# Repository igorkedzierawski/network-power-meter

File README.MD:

# Power Panel with Built-in Energy Analyzer based on ESP32

## Project Description
This project was realized as part of my engineering thesis at the Warsaw University of Technology. The device measures the voltage and current of connected devices. The measured data is transmitted from the device to a web application, where it is analyzed. In real-time, the application processes the gathered data and presents the electrical parameters and visualizations of the voltage and current waveforms to the user.

The device is controlled via the web application – measurements are read, results are visualized, and analysis is performed there. The operation is intuitive:
1. Connect the device to power.
2. Connect to it via Wi-Fi.
3. Connect the device you want to test.
4. Measurement results and analysis are available in the web interface.

The final result of the project is a ready-to-use IoT device.

## System Architecture
The project consists of three main components:

1. **Meter Controller** (ESP32 + measurement circuit) – responsible for Wi-Fi connectivity, menu handling, and managing the measurement circuit.
2. **Backend (ESP32 HTTP/WebSocket Server)** – allows control of the device via HTTP endpoints and fast transmission of measurement results via WebSocket.
3. **Frontend (Angular)** – the web application responsible for controlling the meter, analyzing the received data, and presenting both calculated values and waveform visualizations.
4. **PCB Design** – connects all physical components of the meter control board.

## Web Interface Functionality
- **View Electrical Parameters and Harmonic Analysis** – real-time display of measurement results for voltage, current, and power, as well as THD coefficient and harmonic analysis.
- **Waveform Visualization** – shows measured waveforms on a virtual oscilloscope.
- **Measurement Channel and System Parameter Configuration** – allows setting different channels and adjusting device parameters.
- **Trigger Selection and Analysis Window Width Adjustment** – stabilizes waveform drawing and adjusts measurement precision.
- **Meter Calibration** – adjusts calibration coefficients and selects network frequency (50/60Hz).

## Repository Structure
- **smm-esp32** – Source code for ESP32 (C, ESP-IDF)
- **smm-frontend** – Web application (Angular, TypeScript)
- **smm-pcb** – PCB design (KiCad)

## Device Photos

### Final Device

### Meter Control Board PCB

### Web Interface in Use

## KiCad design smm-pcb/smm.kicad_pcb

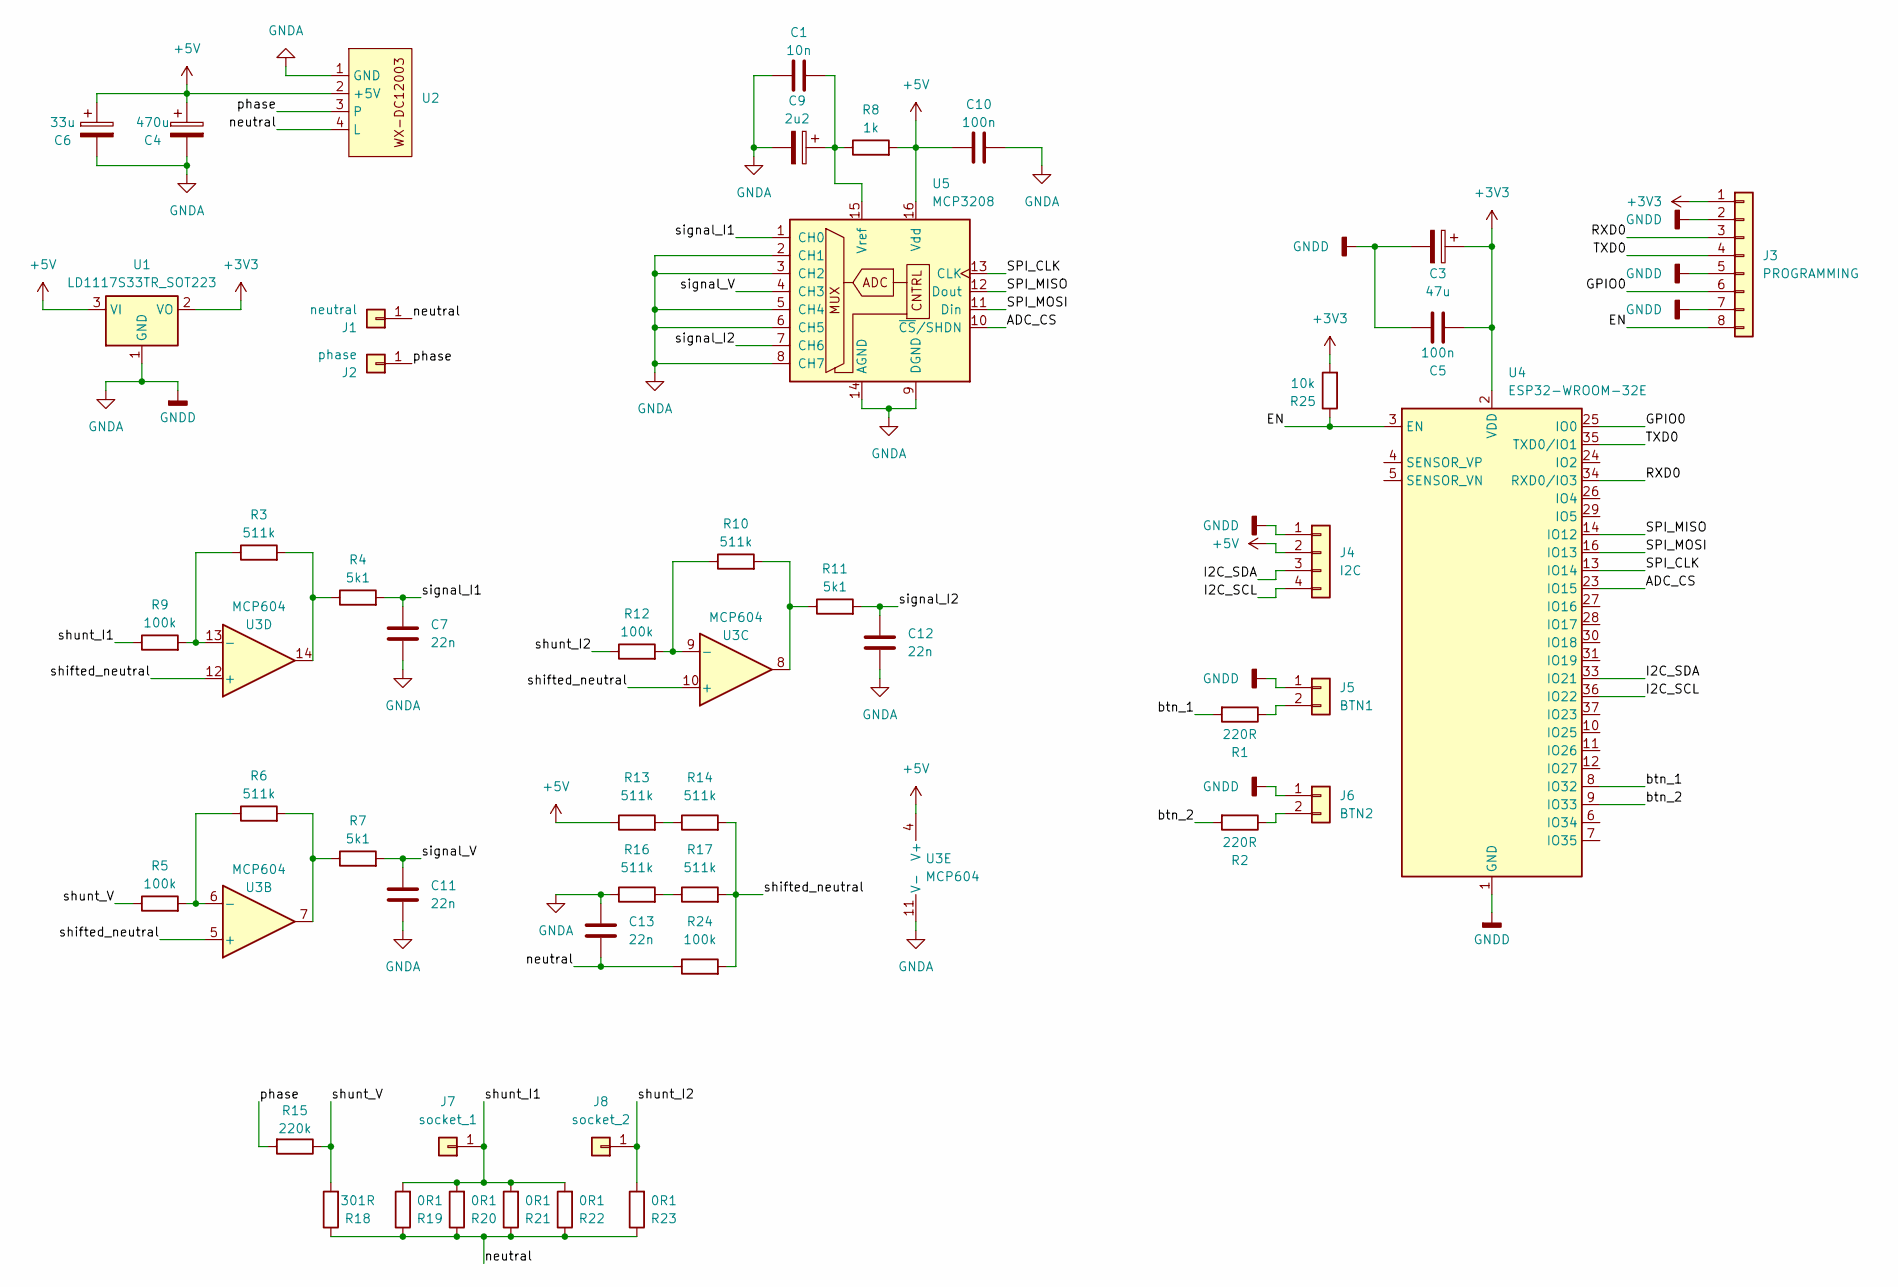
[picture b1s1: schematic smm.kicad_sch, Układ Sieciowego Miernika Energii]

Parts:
C1: 10n; C_Disc_D3.0mm_W2.0mm_P2.50mm
C3: 47u; CP_Radial_D6.3mm_P2.50mm
C4: 470u; CP_Radial_D6.3mm_P2.50mm
C5, C10: 100n; C_Disc_D3.0mm_W2.0mm_P2.50mm
C6: 33u; CP_Radial_D6.3mm_P2.50mm
C7, C11, C12, C13: 22n; C_Disc_D3.0mm_W2.0mm_P2.50mm
C9: 2u2; CP_Radial_D6.3mm_P2.50mm
J1: neutral; spade_connector_6.3_0.8
J2: phase; spade_connector_6.3_0.8
J3: PROGRAMMING; PinHeader_1x08_P2.54mm_Vertical
J4: I2C; PinHeader_1x04_P2.54mm_Vertical
J5: BTN1; PinHeader_1x02_P2.00mm_Vertical
J6: BTN2; PinHeader_1x02_P2.00mm_Vertical
J7: socket_1; spade_connector_6.3_0.8
J8: socket_2; spade_connector_6.3_0.8
R1, R2: 220R; R_Axial_DIN0207_L6.3mm_D2.5mm_P7.62mm_Horizontal
R3, R6, R10, R13, R14, R16, R17: 511k; R_Axial_DIN0207_L6.3mm_D2.5mm_P7.62mm_Horizontal
R4, R7, R11: 5k1; R_Axial_DIN0207_L6.3mm_D2.5mm_P7.62mm_Horizontal
R5, R9, R12, R24: 100k; R_Axial_DIN0207_L6.3mm_D2.5mm_P7.62mm_Horizontal
R8: 1k; R_Axial_DIN0207_L6.3mm_D2.5mm_P7.62mm_Horizontal
R15: 220k; R_Axial_DIN0207_L6.3mm_D2.5mm_P7.62mm_Horizontal
R18: 301R; R_Axial_DIN0207_L6.3mm_D2.5mm_P7.62mm_Horizontal
R19, R20, R21, R22, R23: 0R1; R_Axial_DIN0414_L11.9mm_D4.5mm_P15.24mm_Horizontal
R25: 10k; R_Axial_DIN0207_L6.3mm_D2.5mm_P7.62mm_Horizontal
U1: LD1117S33TR_SOT223; TO-220-3_Vertical
U2: WX-DC12003
U3: MCP604; DIP-14_W7.62mm
U4: ESP32-WROOM-32E; ESP32-WROOM-32D
U5: MCP3208; DIP-16_W7.62mm

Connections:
+3V3: C3.1, C5.1, J3.1, R25.2, U1.2 (VO), U4.2 (VDD)
+5V: C4.1, C6.1, C10.1, J4.2, R8.2, R13.1, U1.3 (VI), U2.2 (+5V), U3.4 (V+), U5.16 (Vdd)
/ADC_CS: U4.23 (IO15), U5.10 (~CS/SHDN)
/EN: J3.8, R25.1, U4.3 (EN)
/GPIO0: J3.6, U4.25 (IO0)
/I2C_SCL: J4.4, U4.36 (IO22)
/I2C_SDA: J4.3, U4.33 (IO21)
/RXD0: J3.3, U4.34 (RXD0/IO3)
/SPI_CLK: U4.13 (IO14), U5.13 (CLK)
/SPI_MISO: U4.14 (IO12), U5.12 (Dout)
/SPI_MOSI: U4.16 (IO13), U5.11 (Din)
/TXD0: J3.4, U4.35 (TXD0/IO1)
/btn_1: R1.2, U4.8 (IO32)
/btn_2: R2.2, U4.9 (IO33)
/neutral: C13.2, J1.1, R18.1, R19.1, R20.1, R21.1, R22.1, R23.1, R24.1, U2.4 (L)
/phase: J2.1, R15.2, U2.3
/shifted_neutral: R14.2, R17.2, R24.2, U3.5 (+), U3.10 (+), U3.12 (+)
/shunt_I1: J7.1, R9.1, R19.2, R20.2, R21.2, R22.2
/shunt_I2: J8.1, R12.1, R23.2
/shunt_V: R5.1, R15.1, R18.2
/signal_I1: C7.1, R4.2, U5.1 (CH0)
/signal_I2: C12.1, R11.2, U5.7 (CH6)
/signal_V: C11.1, R7.2, U5.4 (CH3)
GNDA: C1.1, C3.2, C4.2, C5.2, C6.2, C7.2, C9.2, C10.2, C11.2, C12.2, C13.1, J3.2, J3.5, J3.7, J4.1, J5.1, J6.1, R16.1, U1.1 (GND), U2.1 (GND), U3.11 (V-), U4.1 (GND), U4.15 (GND), U4.38 (GND), U4.39 (GND), U5.2 (CH1), U5.3 (CH2), U5.5 (CH4), U5.6 (CH5), U5.8 (CH7), U5.9 (DGND), U5.14 (AGND)
unnamed: J5.2, R1.1
unnamed: J6.2, R2.1
unnamed: R3.2, R4.1, U3.14
unnamed: R6.2, R7.1, U3.7
unnamed: R10.2, R11.1, U3.8
unnamed: R13.2, R14.1
unnamed: R16.2, R17.1
unnamed: R5.2, R6.1, U3.6 (-)
unnamed: R10.1, R12.2, U3.9 (-)
unnamed: R3.1, R9.2, U3.13 (-)
unnamed: C1.2, C9.1, R8.1, U5.15 (Vref)

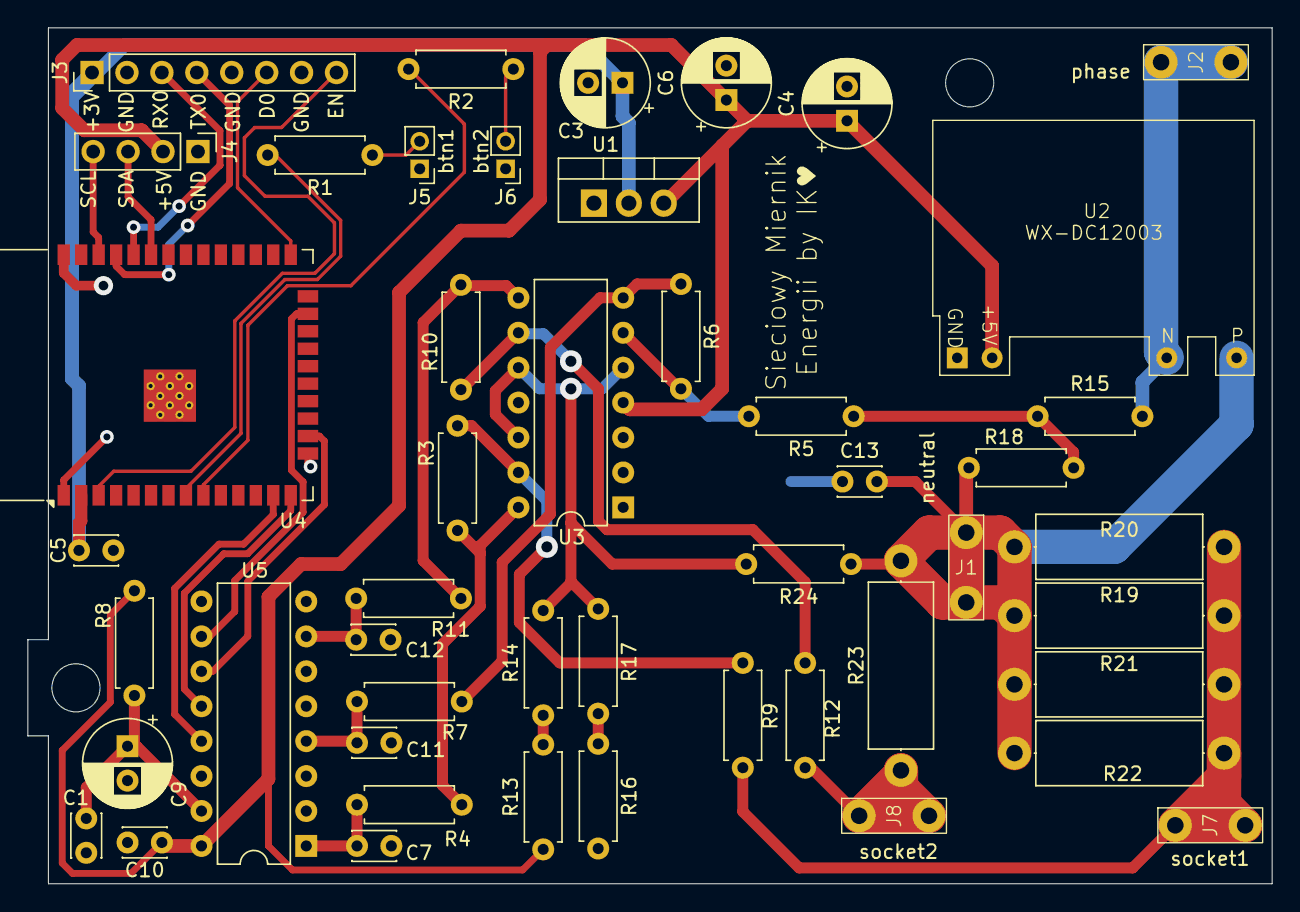
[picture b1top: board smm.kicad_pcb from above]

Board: 2 copper layers, 90.5 x 62.2 mm, 48 parts (0 on the bottom side), 35 nets.

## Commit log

2025-01-28 init commit
